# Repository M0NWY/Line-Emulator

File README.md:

# Line-Emulator
I wanted a thing that would let me connect two modems together, so I could connect my dreamcast to the internet. 
In 2020.
This is the result. It is also a dedicated hotline / intercom thing. Will work with most old analogue phones.
Includes an emulated dial tone with a delay before ringing the other line, standard uk ringing cadence and a timeout if the other line does not answer.

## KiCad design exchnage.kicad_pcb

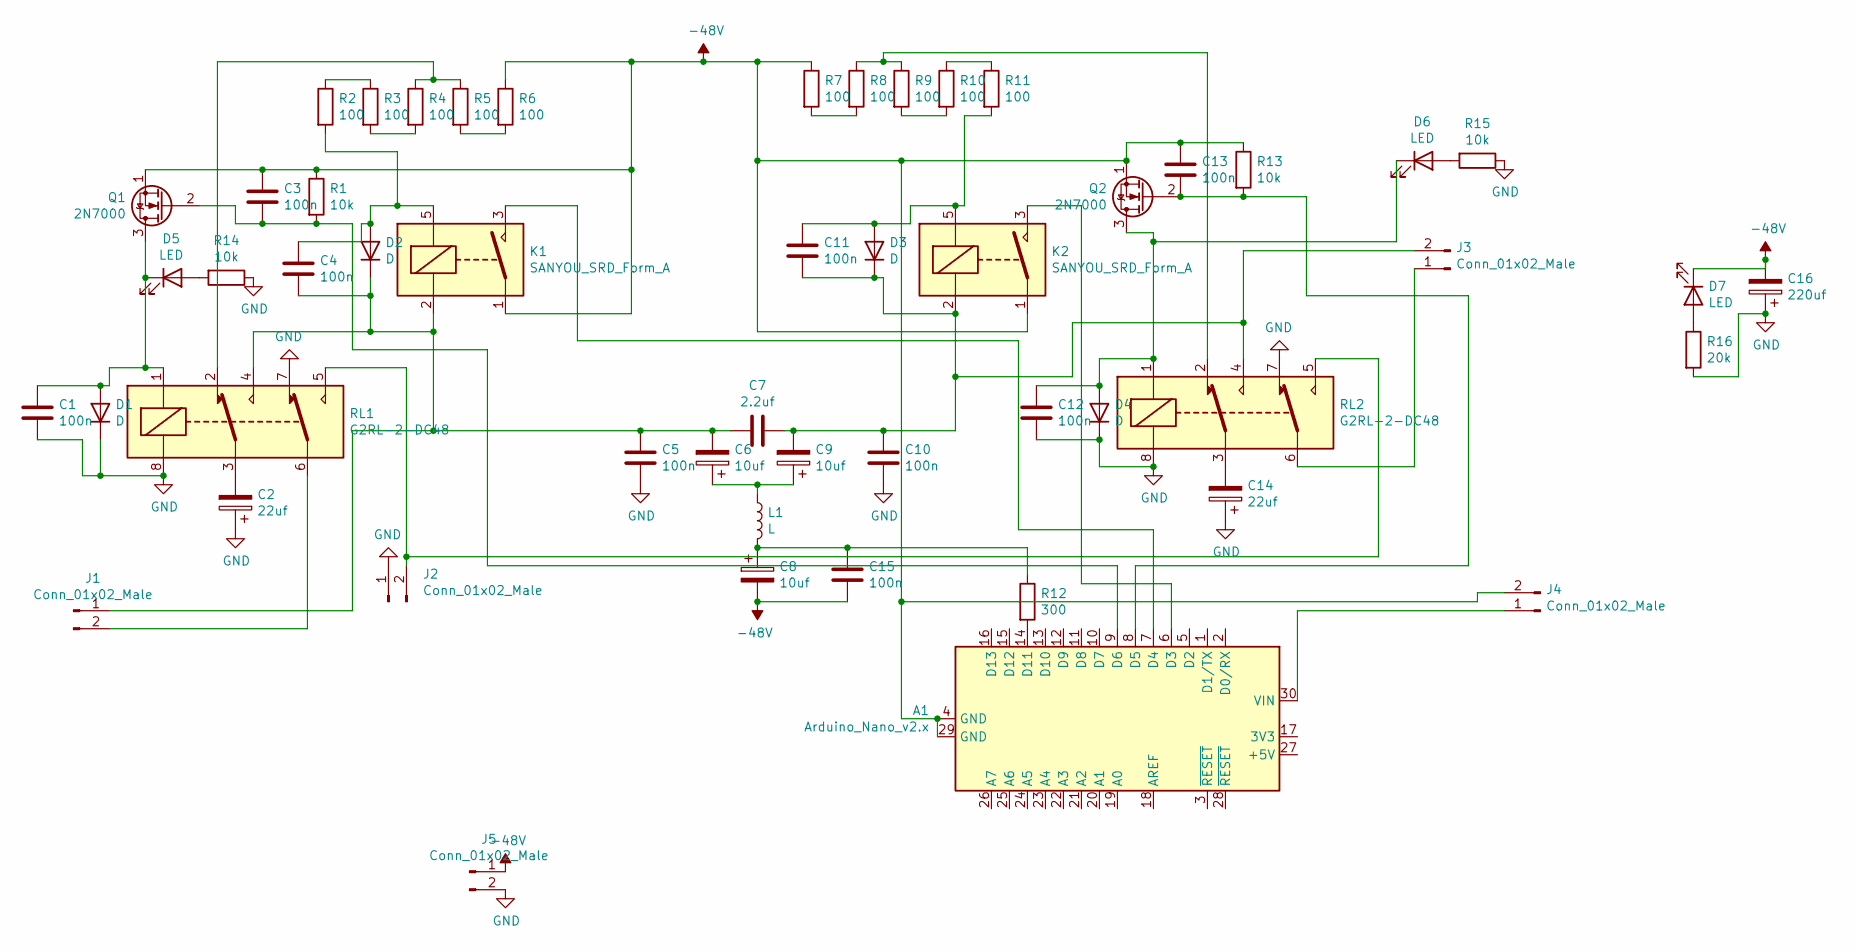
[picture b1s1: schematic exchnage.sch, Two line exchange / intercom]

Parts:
A1: Arduino_Nano_v2.x; Arduino_Nano
C1, C3, C4, C5, C10, C11, C12, C13, C15: 100n; C_Disc_D3.0mm_W1.6mm_P2.50mm
C2, C14: 22uf; CP_Radial_D6.3mm_P2.50mm
C6, C8, C9: 10uf; CP_Radial_D6.3mm_P2.50mm
C7: 2.2uf; C_Rect_L29.0mm_W7.6mm_P27.50mm_MKT
C16: 220uf; CP_Radial_D10.0mm_P5.00mm
D1, D2, D3, D4: D; D_A-405_P10.16mm_Horizontal
D5, D6, D7: LED; LED_D3.0mm
J1, J2, J3, J4, J5: Conn_01x02_Male; PhoenixContact_MSTBVA_2,5_2-G-5,08_1x02_P5.08mm_Vertical
K1, K2: SANYOU_SRD_Form_A; Relay_SPST_SANYOU_SRD_Series_Form_A
L1: L; L_Radial_D7.5mm_P5.00mm_Fastron_07P
Q1, Q2: 2N7000; TO-92_Inline
R1, R13, R14, R15: 10k; R_Axial_DIN0207_L6.3mm_D2.5mm_P10.16mm_Horizontal
R2, R3, R4, R5, R6, R7, R8, R9, R10, R11: 100; R_Axial_DIN0207_L6.3mm_D2.5mm_P10.16mm_Horizontal
R12: 300; R_Axial_DIN0207_L6.3mm_D2.5mm_P10.16mm_Horizontal
R16: 20k; R_Axial_DIN0207_L6.3mm_D2.5mm_P10.16mm_Horizontal
RL1, RL2: G2RL-2-DC48; Relay_DPDT_Omron_G2RL

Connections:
-48V: A1.4 (GND), A1.29 (GND), C3.1, C8.2, C13.1, C15.2, C16.2, D7.1 (K), J4.2, J5.1, K1.1, K2.1, Q1.1 (S), Q2.1 (S), R1.1, R6.1, R7.1, R13.1
GND: C1.2, C2.1, C5.2, C10.2, C12.2, C14.1, C16.1, D1.1 (K), D4.1 (K), J2.1, J5.2, R14.1, R15.1, R16.2, RL1.7, RL1.8, RL2.7, RL2.8
unnamed: A1.6 (D3), K2.3
unnamed: A1.7 (D4), K1.3
unnamed: A1.8 (D5), C13.2, Q2.2 (G), R13.2
unnamed: A1.9 (D6), C3.2, Q1.2 (G), R1.2
unnamed: A1.14 (D11), R12.2
unnamed: A1.30 (VIN), J4.1
unnamed: C1.1, D1.2 (A), D5.1 (K), Q1.3 (D), RL1.1
unnamed: C2.2, RL1.3
unnamed: C4.1, D2.2 (A), K1.5, R2.2
unnamed: C4.2, C5.1, C6.2, C7.2, D2.1 (K), J1.1, K1.2, RL1.4
unnamed: C6.1, C9.1, L1.1
unnamed: C7.1, C9.2, C10.1, C11.2, D3.1 (K), J3.2, K2.2, RL2.4
unnamed: C11.1, D3.2 (A), K2.5, R11.2
unnamed: C12.1, D4.2 (A), D6.1 (K), Q2.3 (D), RL2.1
unnamed: C14.2, RL2.3
unnamed: C8.1, C15.1, L1.2, R12.1
unnamed: D5.2 (A), R14.2
unnamed: D6.2 (A), R15.2
unnamed: D7.2 (A), R16.1
unnamed: J1.2, RL1.6
unnamed: J2.2, RL1.5, RL2.5
unnamed: J3.1, RL2.6
unnamed: R2.1, R3.1
unnamed: R3.2, R4.2
unnamed: R4.1, R5.1, RL1.2
unnamed: R5.2, R6.2
unnamed: R7.2, R8.2
unnamed: R8.1, R9.1, RL2.2
unnamed: R10.1, R11.1
unnamed: R9.2, R10.2

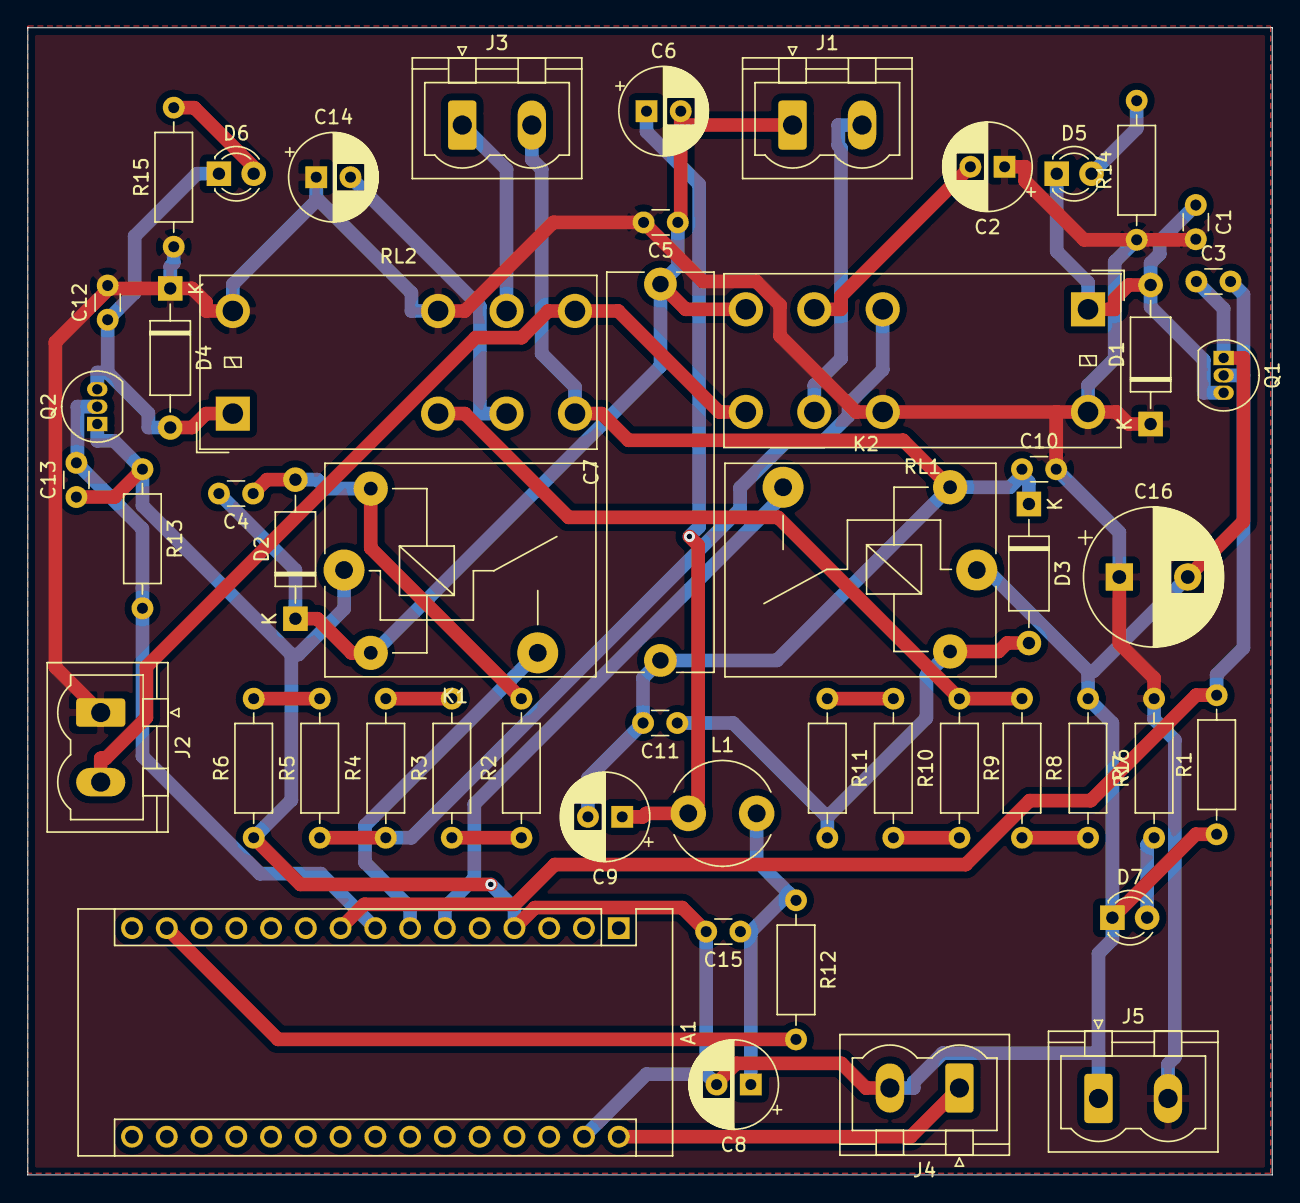
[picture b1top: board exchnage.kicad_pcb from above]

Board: 2 copper layers, 90.9 x 83.8 mm, 52 parts (0 on the bottom side), 32 nets.
